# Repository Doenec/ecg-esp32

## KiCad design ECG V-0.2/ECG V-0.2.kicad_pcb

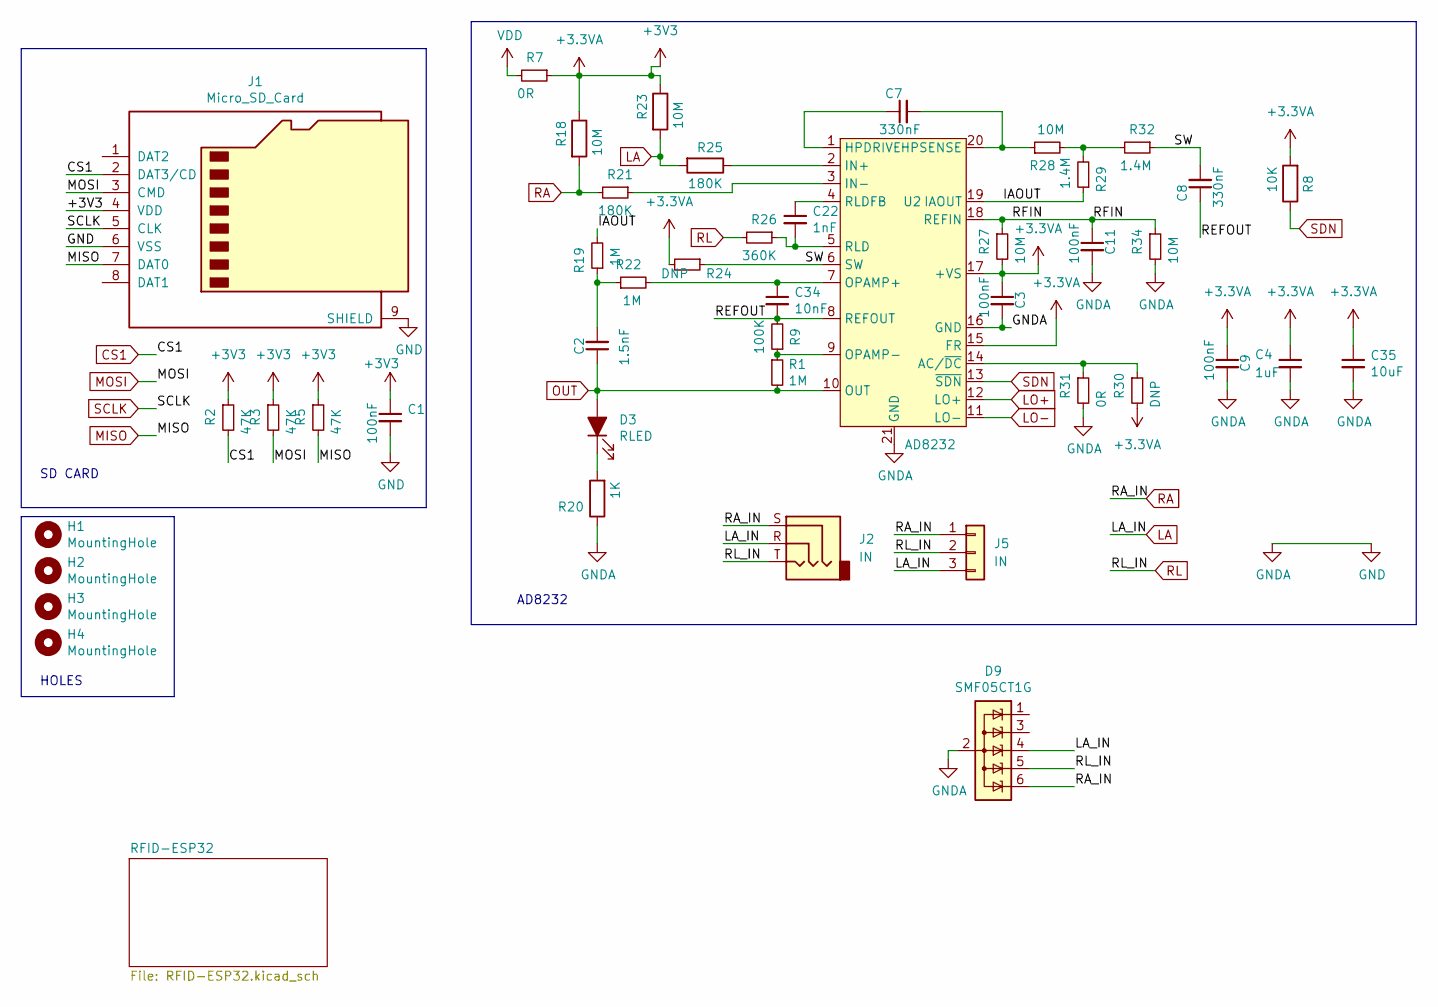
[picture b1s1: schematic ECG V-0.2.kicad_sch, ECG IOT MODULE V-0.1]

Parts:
C1, C3, C9, C11: 100nF; C_0402_1005Metric; MPN CL05B104KO5NNNC; LCSC-PN C1525
C2: 1.5nF; C_0603_1608Metric; MPN 0603B152K500NT; LCSC-PN C1595
C4: 1uF; C_0402_1005Metric; MPN CL05A105KA5NQNC; LCSC-PN C52923
C7, C8: 330nF; C_0603_1608Metric; MPN 0603B334K250NT; LCSC-PN C1615
C22: 1nF; C_0402_1005Metric; MPN 0402B102K500NT; LCSC-PN C1523
C34: 10nF; C_0402_1005Metric; MPN CL05B103KB5NNNC; LCSC-PN C15195
C35: 10uF; C_0402_1005Metric; MPN CL05A106MQ5NUNC; LCSC-PN C15525
D3: RLED; LED_0603_1608Metric; MPN KT-0603R; LCSC-PN C2286
D9: SMF05CT1G; SOT-363_SC-70-6; MPN SMF05CT1G; LCSC-PN C15879
H1, H2, H3, H4: MountingHole; MountingHole_3.2mm_M3_DIN965_Pad
J1: Micro_SD_Card; microSD; MPN TF PUSH; LCSC-PN C393941
J2: IN; PJ-320B; MPN PJ-320B; LCSC-PN C18594
J5: IN; JST_EH_S3B-EH_1x03_P2.50mm_Horizontal
R1, R19, R22: 1M; R_0402_1005Metric; MPN 0402WGF1004TCE; LCSC-PN C26083
R2, R3, R5: 47K; R_0402_1005Metric; MPN 0402WGF4702TCE; LCSC-PN C25792
R7, R31: 0R; R_0402_1005Metric; MPN 0402WGF0000TCE; LCSC-PN C17168
R8: 10K; R_0402_1005Metric; MPN 0402WGF1002TCE; LCSC-PN C25744
R9: 100K; R_0402_1005Metric; MPN 0402WGF1003TCE; LCSC-PN C25741
R18, R23, R27, R28, R34: 10M; R_0402_1005Metric; MPN 0402WGF1005TCE; LCSC-PN C26082
R20: 1K; R_0603_1608Metric; MPN 0603WAF1001T5E; LCSC-PN C21190
R21, R25: 180K; R_0603_1608Metric; MPN 0603WAF1803T5E; LCSC-PN C22827
R24, R30: DNP; R_0402_1005Metric
R26: 360K; R_0603_1608Metric; MPN 0603WAF3603T5E; LCSC-PN C23146
R29, R32: 1.4M; R_0402_1005Metric; MPN 0402WGF1404TCE; LCSC-PN C270644
U2: AD8232; LFCSP-20-1EP_4x4mm_P0.5mm_EP2.5x2.5mm_ThermalVias; MPN AD8232ACPZ-RL; LCSC-PN C652575

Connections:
+3.3VA: C1.1, C3.1, C4.1, C9.1, C35.1, J1.4 (VDD), R2.1, R3.1, R5.1, R7.1, R8.2, R18.1, R23.1, R24.2, R27.2, R30.2, U2.15 (FR), U2.17 (+VS); also elsewhere on the board
/IAOUT: R19.2, R29.1, U2.19 (IAOUT)
/REFOUT: C8.1, C34.2, R9.2, U2.8 (REFOUT)
/RFIN: C11.1, R27.1, R34.1, U2.18 (REFIN)
/SW: C8.2, R24.1, R32.1, U2.6 (SW)
CS1: J1.2 (DAT3/CD), R2.2; also elsewhere on the board
GND: C1.2, C3.2, C4.2, C9.2, C11.2, C35.2, D9.2 (A), J1.6 (VSS), J1.9 (SHIELD), J1.10, J1.11, J1.12, J1.13, R20.1, R31.2, R34.2, U2.16 (GND), U2.21 (GND); also elsewhere on the board
LA: D9.4 (K), J2.R, J5.3, R23.2, R25.2
LO+: U2.12 (LO+); also elsewhere on the board
LO-: U2.11 (LO-); also elsewhere on the board
MISO: J1.7 (DAT0), R5.2; also elsewhere on the board
MOSI: J1.3 (CMD), R3.2; also elsewhere on the board
unnamed: C2.2, R19.1, R22.1
unnamed: D3.1 (K), R20.2
unnamed: R28.2, R29.2, R32.2
unnamed: R30.1, R31.1, U2.14 (AC/~DC)
unnamed: C7.1, U2.1 (HPDRIVE)
unnamed: C7.2, R28.1, U2.20 (HPSENSE)
unnamed: R25.1, U2.2 (IN+)
unnamed: R21.1, U2.3 (IN-)
unnamed: C34.1, R22.2, U2.7 (OPAMP+)
unnamed: R1.1, R9.1, U2.9 (OPAMP-)
unnamed: C22.2, R26.1, U2.5 (RLD)
unnamed: C22.1, U2.4 (RLDFB)
OUT: C2.1, D3.2 (A), R1.2, U2.10 (OUT); also elsewhere on the board
RA: D9.6 (K), J2.S, J5.1, R18.2, R21.2
RL: D9.5 (K), J2.T, J5.2, R26.2
SCLK: J1.5 (CLK); also elsewhere on the board
SDN: R8.1, U2.13 (~SDN)
VDD: R7.2

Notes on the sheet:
AD8232
HOLES
SD CARD

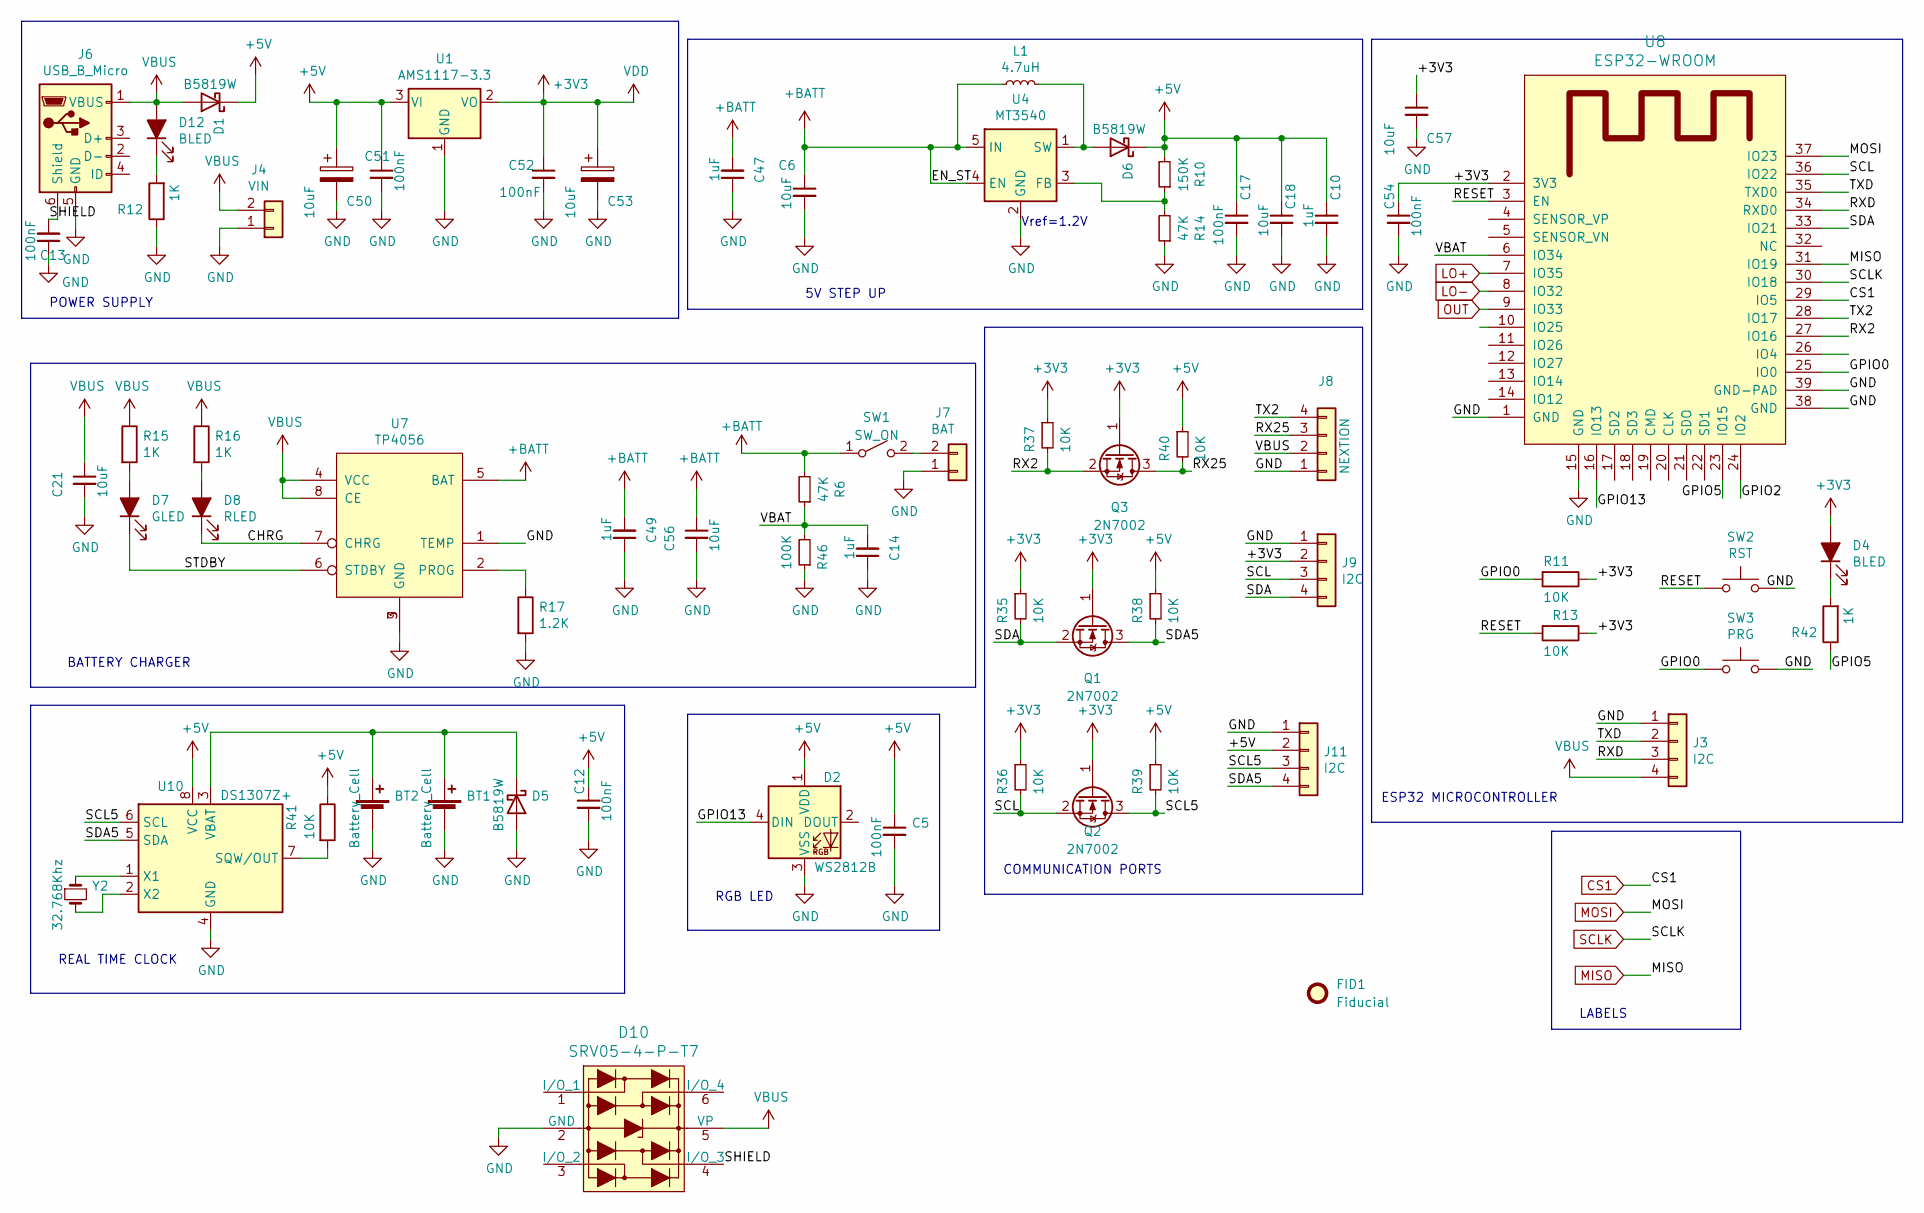
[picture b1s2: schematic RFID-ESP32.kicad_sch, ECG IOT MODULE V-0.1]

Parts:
BT1: Battery_Cell; cr1220-2; MPN CR1220-2; LCSC-PN C70381
BT2: Battery_Cell; PinHeader_1x02_P2.54mm_Vertical
C5, C12, C13, C17, C51, C52, C54: 100nF; C_0402_1005Metric; MPN CL05B104KO5NNNC; LCSC-PN C1525
C6, C18, C50, C53, C57: 10uF; C_0402_1005Metric; MPN CL05A106MQ5NUNC; LCSC-PN C15525
C10, C14, C47, C49: 1uF; C_0402_1005Metric; MPN CL05A105KA5NQNC; LCSC-PN C52923
C21, C56: 10uF; C_0603_1608Metric; MPN 0603X106K160NT; LCSC-PN C70225
D1, D5, D6: B5819W; D_SOD-123; MPN B5819W; LCSC-PN C8598
D2: WS2812B; LED_WS2812B_PLCC4_5.0x5.0mm_P3.2mm; MPN WS2812B-B; LCSC-PN C114586
D4, D12: BLED; LED_0603_1608Metric; MPN 19-217/BHC-ZL1M2RY/3T; LCSC-PN C72041
D7: GLED; LED_0603_1608Metric; MPN 19-217/GHC-YR1S2/3T; LCSC-PN C72043
D8: RLED; LED_0603_1608Metric; MPN KT-0603R; LCSC-PN C2286
D10: SRV05-4-P-T7; SOT-23-6; MPN SRV05-4-P-T7; Digi-Key_PN 1727-3578-1-ND
FID1: Fiducial; Fiducial_0.5mm_Mask1mm
J3, J11: I2C; PinHeader_1x04_P2.54mm_Vertical
J4: VIN; PinHeader_1x02_P2.54mm_Vertical
J6: USB_B_Micro; USB_Micro-B_Molex-105017-0001; MPN 1050170001; LCSC-PN C136000
J7: BAT; JST_EH_B2B-EH-A_1x02_P2.50mm_Vertical
J8: NEXTION; JST_EH_S4B-EH_1x04_P2.50mm_Horizontal
J9: I2C; OLED_I2C_091
L1: 4.7uH; L_1008_2520Metric; MPN LQM2HPN4R7MG0L; LCSC-PN C82314
Q1, Q2, Q3: 2N7002; SOT-23; MPN 2N7002; LCSC-PN C8545
R6, R14: 47K; R_0402_1005Metric; MPN 0402WGF4702TCE; LCSC-PN C25792
R10: 150K; R_0402_1005Metric; MPN 0402WGF1503TCE; LCSC-PN C25755
R11, R13, R35, R36, R37, R38, R39, R40, R41: 10K; R_0402_1005Metric; MPN 0402WGF1002TCE; LCSC-PN C25744
R12, R15, R16, R42: 1K; R_0603_1608Metric; MPN 0603WAF1001T5E; LCSC-PN C21190
R17: 1.2K; R_0402_1005Metric; MPN 0603WAF1201T5E; LCSC-PN C22765
R46: 100K; R_0402_1005Metric; MPN 0402WGF1003TCE; LCSC-PN C25741
SW1: SW_ON; PinHeader_1x02_P2.54mm_Vertical
SW2: RST; SW_SPST_FSMSM; MPN K2-1107ST-A4DW-06; LCSC-PN C118141
SW3: PRG; SW_SPST_FSMSM; MPN K2-1107ST-A4DW-06; LCSC-PN C118141
U1: AMS1117-3.3; SOT-223-3_TabPin2; MPN AMS1117-3.3; LCSC-PN C6186
U4: MT3540; SOT-23-5; MPN MT3540; LCSC-PN C181744
U7: TP4056; HSOP-8-1EP_3.9x4.9mm_P1.27mm_EP2.41x3.1mm_ThermalVias; MPN TP4056-42-ESOP8; LCSC-PN C16581
U8: ESP32-WROOM; ESP32-WROOM-Modif; MPN ESP32-WROOM-32E(4MB); LCSC-PN C82899
U10: DS1307Z+; SOIC-8_3.9x4.9mm_P1.27mm; MPN DS1307Z+T&R; LCSC-PN C9868
Y2: 32.768Khz; Crystal_SMD_G8-2Pin_3.2x1.5mm; MPN Q13FC1350000400; LCSC-PN C32346

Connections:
+3.3VA: C52.1, C53.1, C54.1, C57.1, D4.2 (A), J9.2, Q1.1 (G), Q2.1 (G), Q3.1 (G), R11.1, R13.1, R35.1, R36.1, R37.1, U1.2 (VO), U8.2 (3V3); also elsewhere on the board
+5V: C5.1, C10.1, C12.1, C17.1, C18.1, C50.1, C51.1, D1.1 (K), D2.1 (VDD), D6.1 (K), J11.2, R10.2, R38.1, R39.1, R40.1, R41.1, U1.3 (VI), U10.8 (VCC)
+BATT: C6.1, C47.2, C49.2, C56.1, L1.1, R6.2, SW1.1 (A), U4.4 (EN), U4.5 (IN), U7.5 (BAT)
/RFID-ESP32/CHRG: D8.1 (K), U7.7 (CHRG)
/RFID-ESP32/GPIO0: R11.2, SW3.1, U8.25 (IO0)
/RFID-ESP32/GPIO2: U8.24 (IO2)
/RFID-ESP32/GPIO5: R42.1, U8.23 (IO15)
/RFID-ESP32/GPIO13: D2.4 (DIN), U8.16 (IO13)
/RFID-ESP32/RESET: R13.2, SW2.1, U8.3 (EN)
/RFID-ESP32/RX2: Q3.2 (S), R37.2, U8.27 (IO16)
/RFID-ESP32/RX25: J8.3, Q3.3 (D), R40.2
/RFID-ESP32/RXD: J3.3, U8.34 (RXD0)
/RFID-ESP32/SCL: J9.3, Q2.2 (S), R36.2, U8.36 (IO22)
/RFID-ESP32/SCL5: J11.3, Q2.3 (D), R39.2, U10.6 (SCL)
/RFID-ESP32/SDA: J9.4, Q1.2 (S), R35.2, U8.33 (IO21)
/RFID-ESP32/SDA5: J11.4, Q1.3 (D), R38.2, U10.5 (SDA)
/RFID-ESP32/SHIELD: C13.2, D10.4 (I/O_3), J6.6 (Shield)
/RFID-ESP32/STDBY: D7.1 (K), U7.6 (STDBY)
/RFID-ESP32/TX2: J8.4, U8.28 (IO17)
/RFID-ESP32/TXD: J3.2, U8.35 (TXD0)
/RFID-ESP32/VBAT: C14.2, R6.1, R46.2, U8.6 (IO34)
CS1: U8.29 (IO5); also elsewhere on the board
GND: BT1.2 (-), BT2.2 (-), C5.2, C6.2, C10.2, C12.2, C13.1, C14.1, C17.2, C18.2, C21.2, C47.1, C49.1, C50.2, C51.2, C52.2, C53.2, C54.2, C56.2, C57.2, D2.3 (VSS), D5.2 (A), D10.2 (GND), J3.1, J4.1, J6.5 (GND), J7.1, J8.1, J9.1, J11.1, R12.1, R14.1, R17.2, R46.1, SW2.2, SW3.2, U1.1 (GND), U4.2 (GND), U7.1 (TEMP), U7.3 (GND), U7.9 (GND), U8.1 (GND), U8.15 (GND), U8.38 (GND), U8.39 (GND-PAD), U10.4 (GND); also elsewhere on the board
LO+: U8.7 (IO35); also elsewhere on the board
LO-: U8.8 (IO32); also elsewhere on the board
MISO: U8.31 (IO19); also elsewhere on the board
MOSI: U8.37 (IO23); also elsewhere on the board
unnamed: BT1.1 (+), BT2.1 (+), D5.1 (K), U10.3 (VBAT)
unnamed: D4.1 (K), R42.2
unnamed: D6.2 (A), L1.2, U4.1 (SW)
unnamed: D7.2 (A), R15.2
unnamed: D8.2 (A), R16.2
unnamed: D12.1 (K), R12.2
unnamed: J7.2, SW1.2 (B)
unnamed: R10.1, R14.2, U4.3 (FB)
unnamed: R17.1, U7.2 (PROG)
unnamed: R41.2, U10.7 (SQW/OUT)
unnamed: U10.1 (X1), Y2.1
unnamed: U10.2 (X2), Y2.2
OUT: U8.9 (IO33); also elsewhere on the board
SCLK: U8.30 (IO18); also elsewhere on the board
VBUS: C21.1, D1.2 (A), D10.5 (VP), D12.2 (A), J3.4, J4.2, J6.1 (VBUS), J8.2, R15.1, R16.1, U7.4 (VCC), U7.8 (CE)

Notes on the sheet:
ESP32 MICROCONTROLLER
LABELS
REAL TIME CLOCK
COMMUNICATION PORTS
POWER SUPPLY
5V STEP UP
BATTERY CHARGER
Vref=1.2V
RGB LED

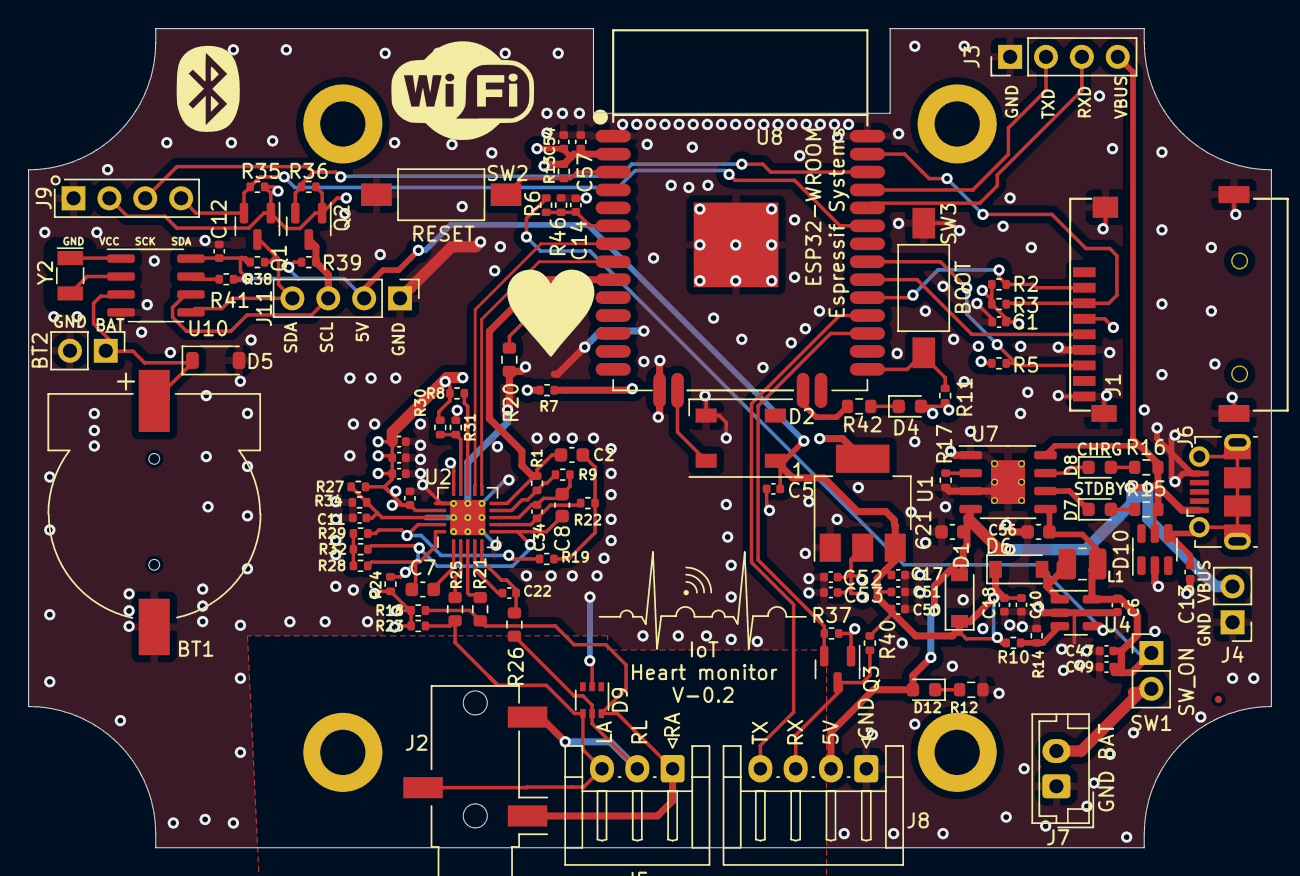
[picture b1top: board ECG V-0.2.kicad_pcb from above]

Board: 4 copper layers, 88.0 x 58.0 mm, 112 parts (0 on the bottom side), 61 nets.

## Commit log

2024-11-03 kicad files
